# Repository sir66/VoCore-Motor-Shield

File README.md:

# VoCore-Motor-Shield
Connection shield for using Pololu DRV8835 Dual Motor Driver Carrier and S7V7F5 Voltage Regulator with VoCore coin-size computer http://vocore.io/ https://www.pololu.com/product/2135 https://www.pololu.com/product/2119

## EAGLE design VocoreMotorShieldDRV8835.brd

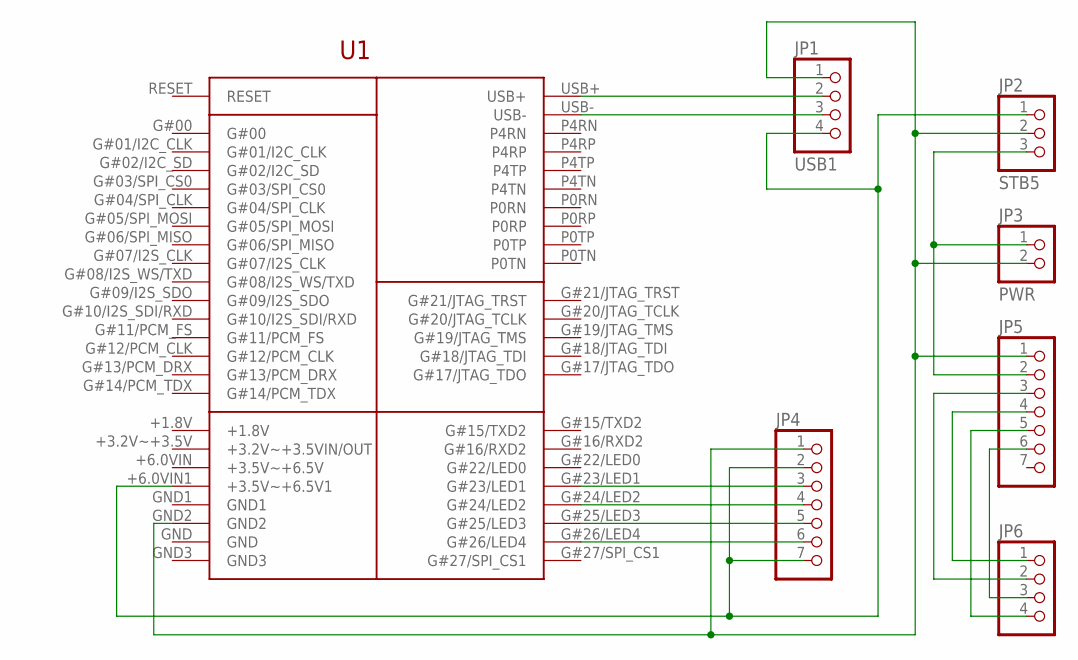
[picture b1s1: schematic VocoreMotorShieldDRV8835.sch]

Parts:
JP1: USB1; 1X04
JP2: STB5; 1X03
JP3: PWR; 1X02
JP4, JP5: PINHD-1X7; 1X07
JP6: PINHD-1X4; 1X04
U1: VOCORE_SHIELD; VOCORE_DOC_CUSTOM

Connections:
unnamed: JP1.1, JP2.2, JP3.2, JP4.1, JP5.1, U1.GND2
unnamed: JP2.3, JP3.1, JP5.2
unnamed: JP1.4, JP2.1, JP4.2, JP4.7, U1.+6.0VIN1 (+3.5V~+6.5V1)
unnamed: JP4.3, U1.G#23/LED1
unnamed: JP1.3, U1.USB-
unnamed: JP1.2, U1.USB+
unnamed: JP4.4, U1.G#24/LED2
unnamed: JP4.5, U1.G#25/LED3
unnamed: JP4.6, U1.G#26/LED4
unnamed: JP5.4, JP6.1
unnamed: JP5.3, JP6.2
unnamed: JP5.5, JP6.4
unnamed: JP5.6, JP6.3

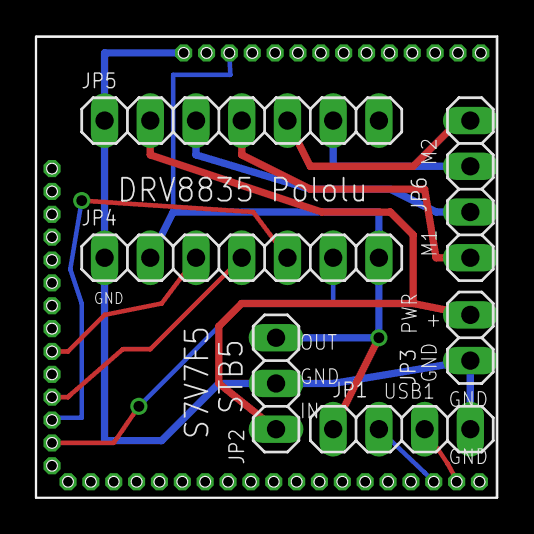
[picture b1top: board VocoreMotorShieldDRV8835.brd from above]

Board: 2 copper layers, 25.7 x 25.7 mm, 7 parts (0 on the bottom side), 13 nets.

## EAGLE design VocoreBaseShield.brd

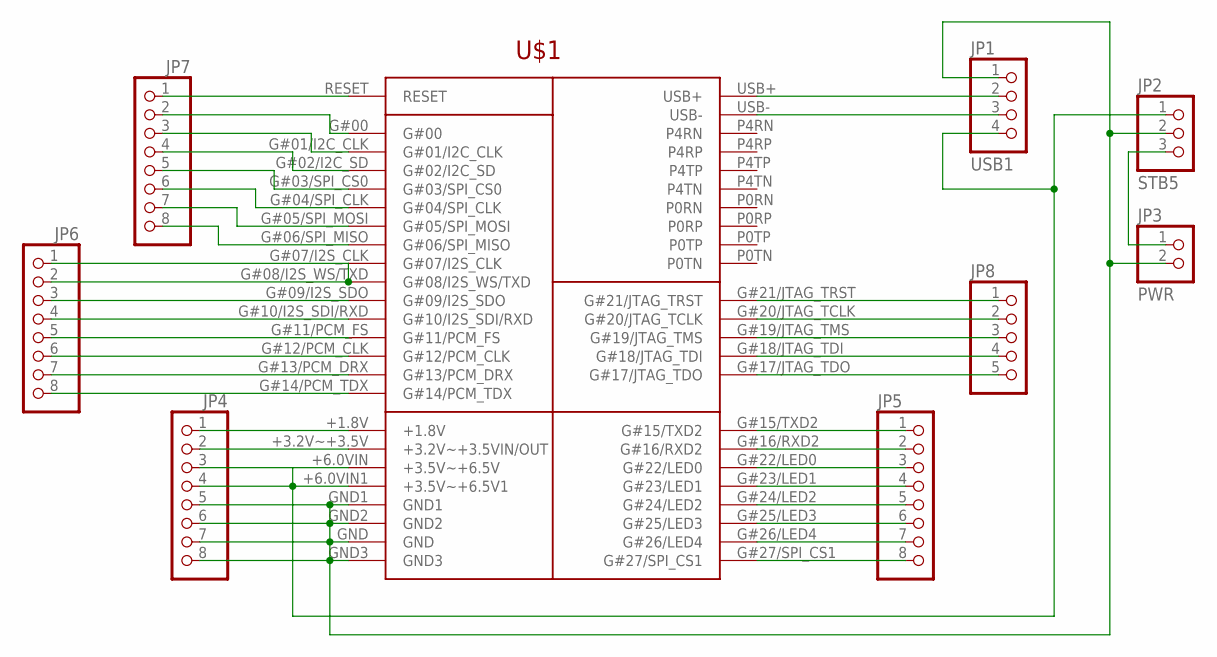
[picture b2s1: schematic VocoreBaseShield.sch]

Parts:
JP1: USB1; 1X04
JP2: STB5; 1X03
JP3: PWR; 1X02
JP4, JP5, JP6, JP7: PINHD-1X8; 1X08
JP8: PINHD-1X5; 1X05
U$1: VOCORE_SHIELD; VOCORE_DOC_CUSTOM

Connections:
unnamed: JP1.1, JP2.2, JP3.2, JP4.5, JP4.6, JP4.7, JP4.8, U$1.GND, U$1.GND1, U$1.GND2, U$1.GND3
unnamed: JP2.3, JP3.1
unnamed: JP1.4, JP2.1, JP4.3, JP4.4, U$1.+6.0VIN (+3.5V~+6.5V), U$1.+6.0VIN1 (+3.5V~+6.5V1)
unnamed: JP4.1, U$1.+1.8V
unnamed: JP1.3, U$1.USB-
unnamed: JP1.2, U$1.USB+
unnamed: JP4.2, U$1.+3.2V~+3.5V (+3.2V~+3.5VIN/OUT)
unnamed: JP5.1, U$1.G#15/TXD2
unnamed: JP5.2, U$1.G#16/RXD2
unnamed: JP5.3, U$1.G#22/LED0
unnamed: JP5.4, U$1.G#23/LED1
unnamed: JP5.5, U$1.G#24/LED2
unnamed: JP5.6, U$1.G#25/LED3
unnamed: JP5.7, U$1.G#26/LED4
unnamed: JP5.8, U$1.G#27/SPI_CS1
unnamed: JP6.8, U$1.G#14/PCM_TDX
unnamed: JP6.7, U$1.G#13/PCM_DRX
unnamed: JP6.6, U$1.G#12/PCM_CLK
unnamed: JP6.5, U$1.G#11/PCM_FS
unnamed: JP6.4, U$1.G#10/I2S_SDI/RXD
unnamed: JP6.3, U$1.G#09/I2S_SDO
unnamed: JP6.1, JP6.2, U$1.G#08/I2S_WS/TXD
unnamed: JP7.1, U$1.RESET
unnamed: JP7.2, U$1.G#00
unnamed: JP7.3, U$1.G#01/I2C_CLK
unnamed: JP7.4, U$1.G#02/I2C_SD
unnamed: JP7.5, U$1.G#03/SPI_CS0
unnamed: JP7.6, U$1.G#04/SPI_CLK
unnamed: JP7.7, U$1.G#05/SPI_MOSI
unnamed: JP7.8, U$1.G#06/SPI_MISO
unnamed: JP8.2, U$1.G#20/JTAG_TCLK
unnamed: JP8.4, U$1.G#18/JTAG_TDI
unnamed: JP8.1, U$1.G#21/JTAG_TRST
unnamed: JP8.5, U$1.G#17/JTAG_TDO

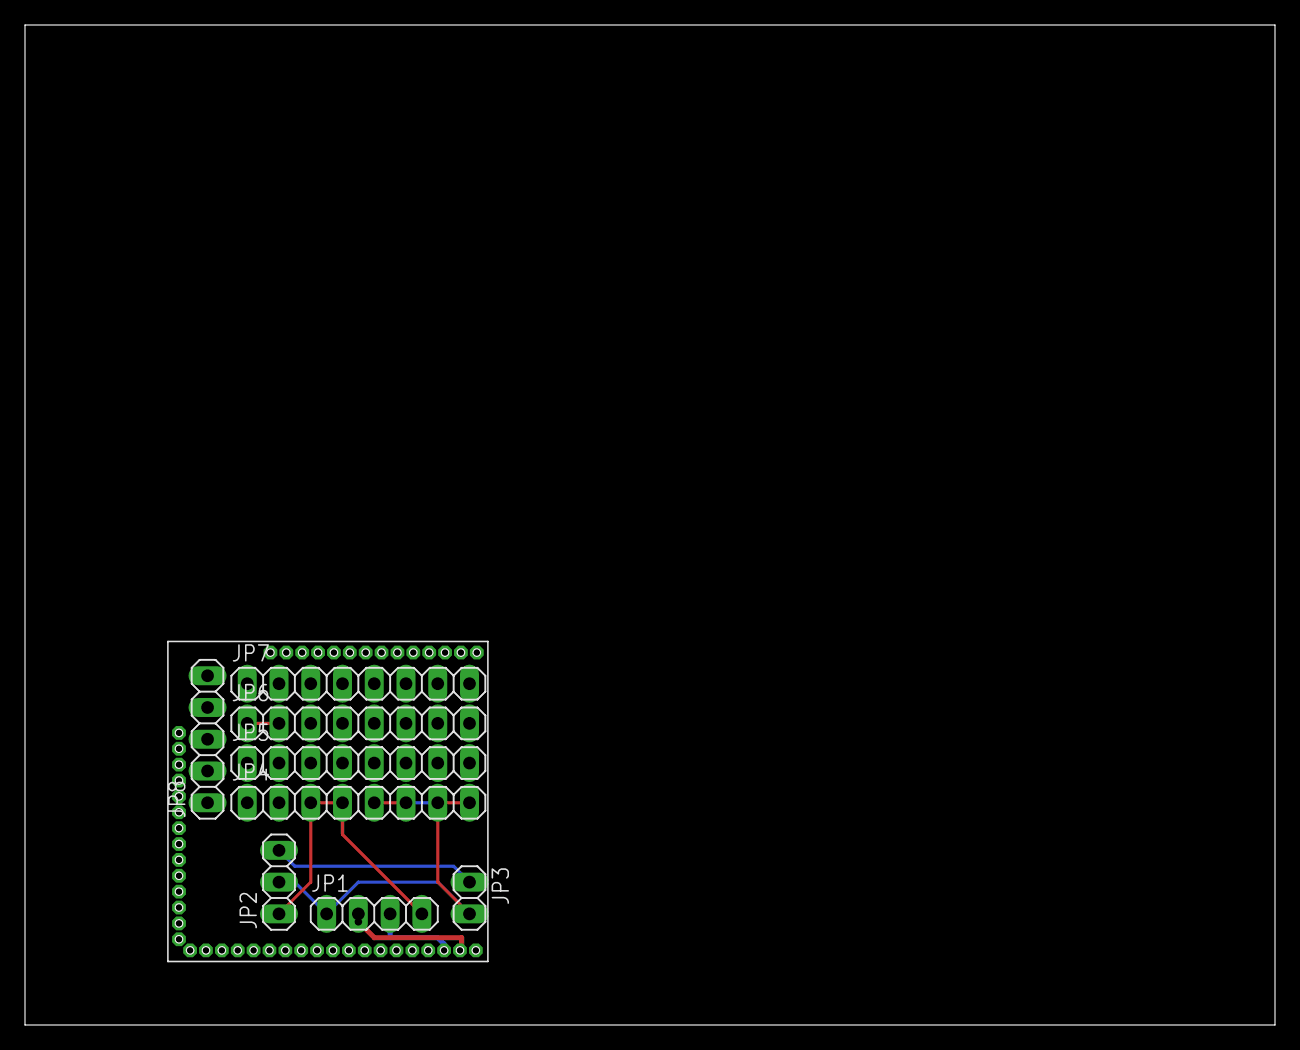
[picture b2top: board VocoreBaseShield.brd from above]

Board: 2 copper layers, 100.0 x 80.0 mm, 9 parts (0 on the bottom side), 34 nets.

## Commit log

2015-02-08 First version
2015-02-08 Version 0.1
2015-02-08 Revert "Version 0.1"
    This reverts commit b4409390f012a34cf1db7157863f4cbc9e08abe1.
2015-02-08 Version 0.2
2015-02-08 Version 0.3
2015-02-08 Create motor
